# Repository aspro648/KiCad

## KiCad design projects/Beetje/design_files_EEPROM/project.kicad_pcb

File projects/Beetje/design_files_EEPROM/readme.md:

Beetje Blok Template

Based on https://jeelabs.org/2009/09/19/memory-plug-v1/

https://playground.arduino.cc/code/I2CEEPROM
https://www.instructables.com/id/Add-I2C-EEPROM-to-Arduino/
https://learn.sparkfun.com/tutorials/reading-and-writing-serial-eeproms

Bill Of Materials
----------------
  
- 1 ea., Perfect Purple PCB from OSH Park, with not so perfect layout from [project.kicad_pcb](project.kicad_pcb) file.
- 1 ea., C1 CAP CER 0.1UF 50V X7R 0805, https://www.digikey.com/short/j58qjp
- 1 ea., R1, R2 4K7 0805 SMD Resistor, https://www.digikey.com/short/j2d0wd

- 1 ea., U1, 24LC1025-I/SN-ND 1Mbit 8-SOIC, https://www.digikey.com/short/jwmp8v ($2.95), or
- 1 ea., U1, CAT24M01WI-GT3IC 1Mbit 8-SOIC, https://www.digikey.com/short/jwmpp7 ($1.33), or
RM24C512C FRAM 512K, https://www.digikey.com/short/jwmpqm ???
 or
- 1 ea., U1, IC EEPROM 1M I2C 400KHZ 8SOIC, https://www.digikey.com/short/jf10h0

Revisions
----------------
0.1 Sep 2018 Footprints from 0603 to 0805

License
----------------
[Attribution-ShareAlike 3.0 United States (CC BY-SA 3.0 US)](https://creativecommons.org/licenses/by-sa/3.0/us/)

You are free to:

- Share — copy and redistribute the material in any medium or format
- Adapt — remix, transform, and build upon the material

Under the following terms:

- Attribution — You must give appropriate credit, provide a link to the license, and indicate if changes were made. You may do so in any reasonable manner, but not in any way that suggests the licensor endorses you or your use.
- ShareAlike — If you remix, transform, or build upon the material, you must distribute your contributions under the same license as the original.

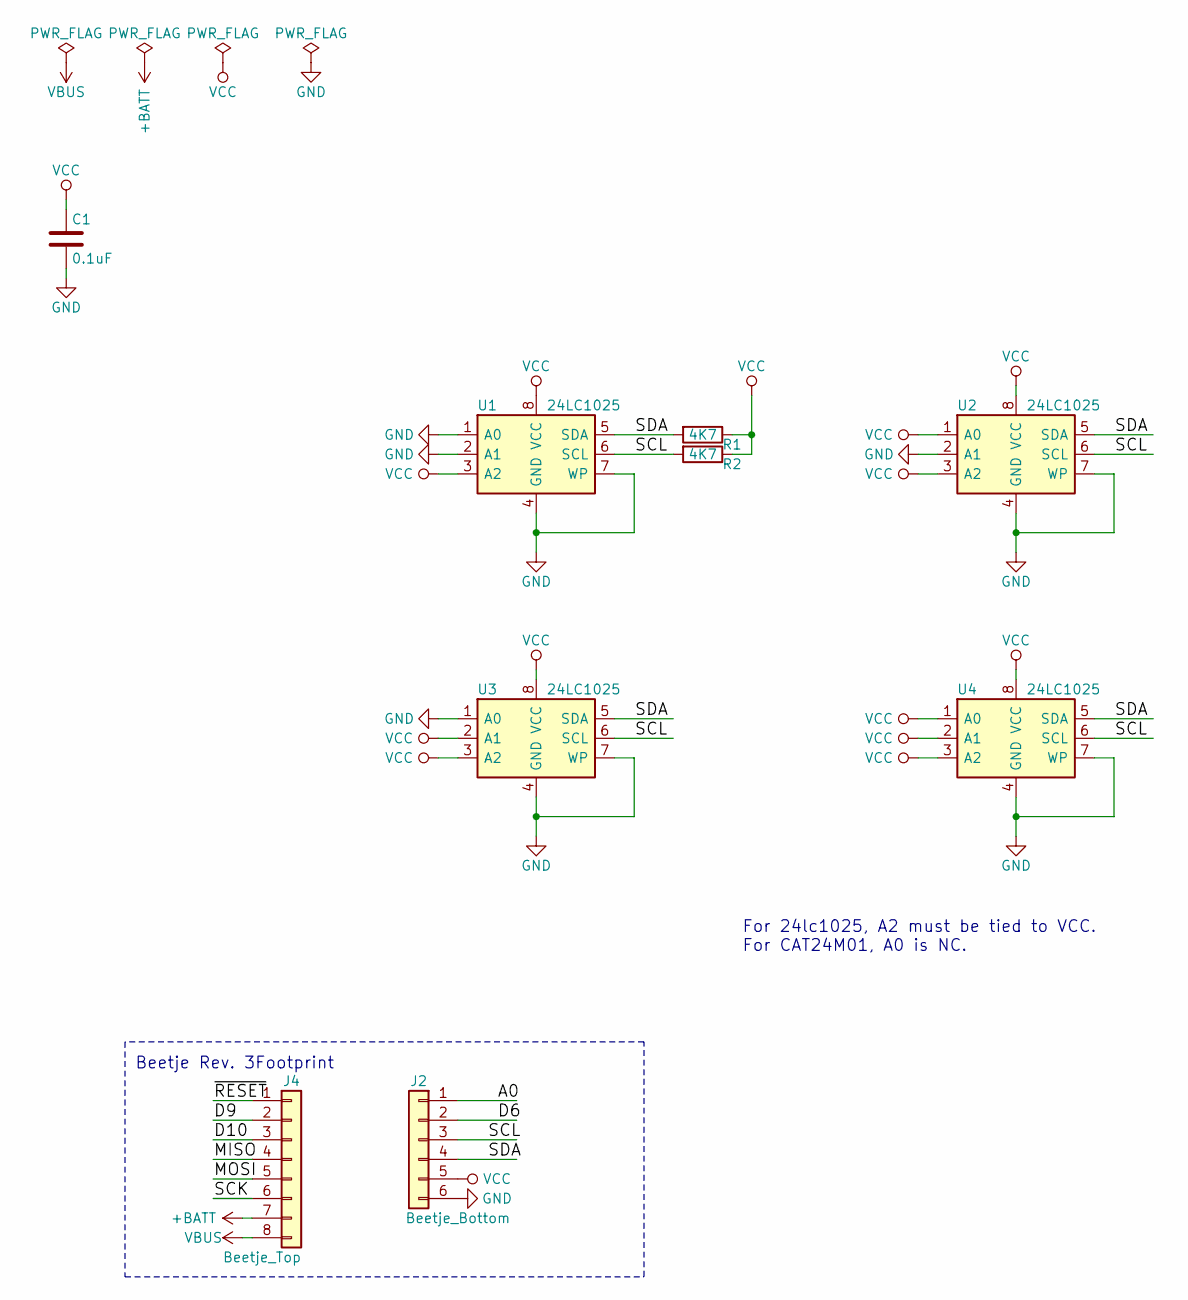
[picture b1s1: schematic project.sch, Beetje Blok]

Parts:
C1: 0.1uF; C_0603
J2: Beetje_Bottom; Pin_Header_Straight_1x06_Pitch2.54mm
J4: Beetje_Top; Pin_Header_Straight_1x08_Pitch2.54mm
R1, R2: 4K7; R_0603
U1, U2, U3, U4: 24LC1025; SOIC-8_3.9x4.9mm_Pitch1.27mm

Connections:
+BATT: J4.7
/A0: J2.1
/D6: J2.2
/D9: J4.2
/D10: J4.3
/MISO: J4.4
/MOSI: J4.5
/SCK: J4.6
/SCL: J2.3, R2.2, U1.6 (SCL), U2.6 (SCL), U3.6 (SCL), U4.6 (SCL)
/SDA: J2.4, R1.2, U1.5 (SDA), U2.5 (SDA), U3.5 (SDA), U4.5 (SDA)
/~RESET: J4.1
GND: C1.2, J2.6, U1.1 (A0), U1.2 (A1), U1.4 (GND), U1.7 (WP), U2.2 (A1), U2.4 (GND), U2.7 (WP), U3.1 (A0), U3.4 (GND), U3.7 (WP), U4.4 (GND), U4.7 (WP)
VBUS: J4.8
VCC: C1.1, J2.5, R1.1, R2.1, U1.3 (A2), U1.8 (VCC), U2.1 (A0), U2.3 (A2), U2.8 (VCC), U3.2 (A1), U3.3 (A2), U3.8 (VCC), U4.1 (A0), U4.2 (A1), U4.3 (A2), U4.8 (VCC)

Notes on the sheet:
Beetje Rev. 3Footprint
For 24lc1025, A2 must be tied to VCC. For CAT24M01, A0 is NC.

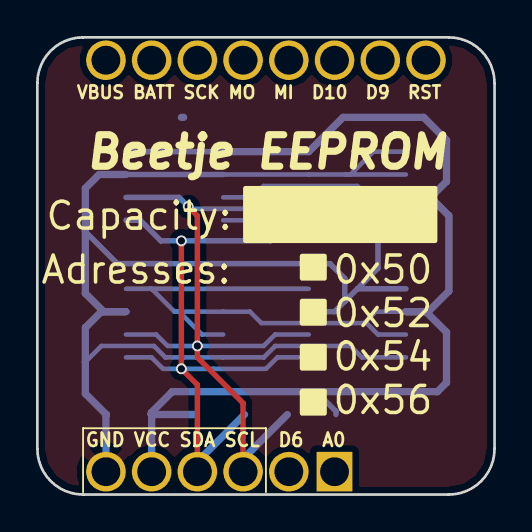
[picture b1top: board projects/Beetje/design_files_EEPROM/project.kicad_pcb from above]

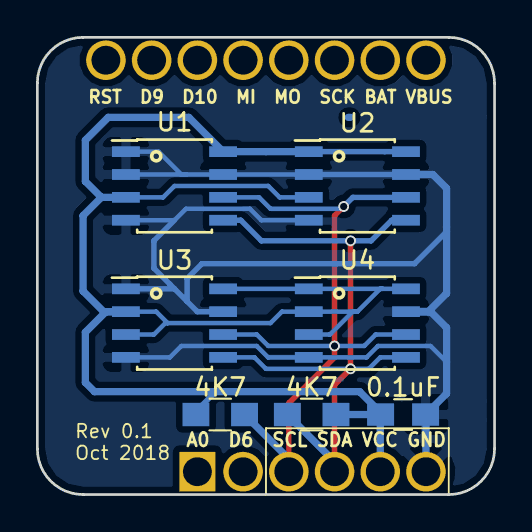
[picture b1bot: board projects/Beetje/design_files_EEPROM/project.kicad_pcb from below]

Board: 2 copper layers, 25.4 x 25.4 mm, 9 parts (7 on the bottom side), 4 nets.

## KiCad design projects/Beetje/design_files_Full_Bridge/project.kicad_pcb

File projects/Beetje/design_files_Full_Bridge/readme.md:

Beetje Full Bridge

Full bridge motor driver using Ti DRV8871.  Capable of 6.5V ~ 45V output at 3.6A.  Current can be limited by resistor settings.

D10	D11	MTR_A 	MTR_B
0	0	Hi-Z	Hi-Z
0	1	L 		H
1	0	H 		L
1	1	L 		L   (brake, low-side slow decay)

Project website: https://hackaday.io/project/160638-beetje-bloks

Bill Of Materials
----------------
  
- 1 ea., Perfect Purple PCB from OSH Park, with not so perfect layout from [project.kicad_pcb](project.kicad_pcb) file.
- 1 ea., U1 DRV8871 IC MOTOR DRIVER, https://www.digikey.com/short/p877rm 
- 1 ea., U2 MCP2031 I2C ADC SO23-5, MCP3021A1T-E/OT (address 0x49) https://www.digikey.com/short/p877wq
- 1 ea., CAP CER 0.1UF 50V X7R 0805, https://www.digikey.com/short/pq0ncp 
- 1 ea., CAP 47UF 63V SMD 8.3mm, https://www.digikey.com/short/p87c9p
- 1 ea., D6 LED SMD 0805, https://www.digikey.com/short/jwf4nw
- 1 ea., R1 SMD 0805, Current limiting 
	- 3.5A  18K Ohm, https://www.digikey.com/short/p8779m
	- 3A 22K Ohm, https://www.digikey.com/short/p8779n
	- 2A 33K Ohm, https://www.digikey.com/short/p87791
	- 1A 62K Ohm, https://www.digikey.com/short/p877bq
- 1 ea., R2 1K SMD 0805, https://www.digikey.com/short/j2d0wt
- 2 ea., J1, J3 TERM BLOCK PCB 2POS 5.0MM GREEN, Phoenix 1935161 https://www.digikey.com/short/jnrmvw
- 1 ea., 64-pin header(enough for 4.5 boards) Mill-max 311-43-164-41-001000, https://www.digikey.com/short/jnqdm2

Revisions
------------------
0.1 Rename to Full bridge, because that is what it is, I learned.

License
----------------
[Attribution-ShareAlike 3.0 United States (CC BY-SA 3.0 US)](https://creativecommons.org/licenses/by-sa/3.0/us/)

You are free to:

- Share — copy and redistribute the material in any medium or format
- Adapt — remix, transform, and build upon the material

Under the following terms:

- Attribution — You must give appropriate credit, provide a link to the license, and indicate if changes were made. You may do so in any reasonable manner, but not in any way that suggests the licensor endorses you or your use.
- ShareAlike — If you remix, transform, or build upon the material, you must distribute your contributions under the same license as the original.

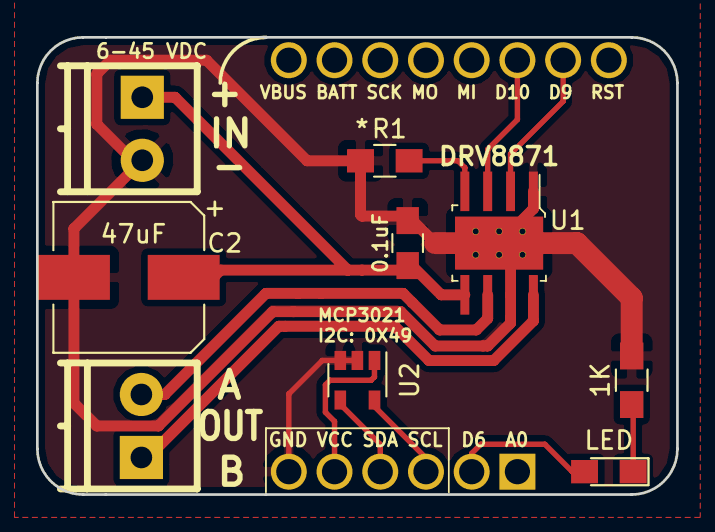
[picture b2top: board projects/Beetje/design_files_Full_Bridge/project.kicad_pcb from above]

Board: 2 copper layers, 35.6 x 25.4 mm, 12 parts (0 on the bottom side), 12 nets.

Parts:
C1: 0.1uF; C_0805_HandSoldering
C2: 47uF; CP_Elec_8x10
D6: LED; LED_0805_HandSoldering
J1: Conn_01x02; terminal_mirror
J2: Beetje_Bottom
J3: Conn_01x02; terminal
J4: Beetje_Top
R1: *; R_0805_HandSoldering
R2: 1K; R_0805_HandSoldering
U1: DRV8871DDA; PowerSOIC-8_W3.9mm
U2: MCP3021; SOT-23-5
VAL: MadeInOregonRev25

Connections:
/D6: D6.2, J2.2
/D9: J4.2, U1.2
/D10: J4.3, U1.3
/MTR_A: J3.2, U1.6
/MTR_B: J3.1, U1.8
/SCL: J2.3, U2.5
/SDA: J2.4, U2.4
/VMTR: C1.1, C2.1, J1.1, U1.5
GND: C1.2, C2.2, J1.2, J2.6, R1.2, R2.1, U1.1, U1.7, U1.9, U2.2, U2.3
unnamed: D6.1, R2.2
unnamed: R1.1, U1.4
VCC: J2.5, U2.1

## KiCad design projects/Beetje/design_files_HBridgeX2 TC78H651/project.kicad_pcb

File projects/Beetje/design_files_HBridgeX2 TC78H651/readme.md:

Beetje H-Bridge

Project website: https://hackaday.io/project/160638-beetje-bloks

Bill Of Materials
----------------
  
- 1 ea., Perfect Purple PCB from OSH Park, with not so perfect layout from [project.kicad_pcb](project.kicad_pcb) file.
- 1 ea., TC78H651FNG IC MOTOR DRIVER 16TSSOP, https://www.digikey.com/short/z8r9nr
- 1 ea., CAP CER 10UF 25V 1206, https://www.digikey.com/short/j29pwm
- 1 ea., CAP CER 1UF 16V X7R 0805, https://www.digikey.com/short/z8dz2m
- 1 ea., TRIMMER 10K OHM 0.1W J LEAD TOP, https://www.digikey.com/short/zq5dpc
- 1 ea., D2 LED SMD 0805, https://www.digikey.com/short/jwf4nw
- 4 ea., R3-R8 10K SMD 0805, https://www.digikey.com/short/j2d0w4 
- 1 ea., R2 1K SMD 0805, https://www.digikey.com/short/j2d0wt
- 3 ea., J1, J3, J5 TERM BLOCK PCB 2POS 5.0MM GREEN, Phoenix 1935161 https://www.digikey.com/short/jnrmvw
- 1 ea., 64-pin header(enough for 4.5 boards) Mill-max 311-43-164-41-001000, https://www.digikey.com/short/jnqdm2

Revisions
------------------
0.3 Switched from TB6612FNG to TC78H651FNG, added potentiometer, removed MCP chip.

License
----------------
[Attribution-ShareAlike 3.0 United States (CC BY-SA 3.0 US)](https://creativecommons.org/licenses/by-sa/3.0/us/)

You are free to:

- Share — copy and redistribute the material in any medium or format
- Adapt — remix, transform, and build upon the material

Under the following terms:

- Attribution — You must give appropriate credit, provide a link to the license, and indicate if changes were made. You may do so in any reasonable manner, but not in any way that suggests the licensor endorses you or your use.
- ShareAlike — If you remix, transform, or build upon the material, you must distribute your contributions under the same license as the original.

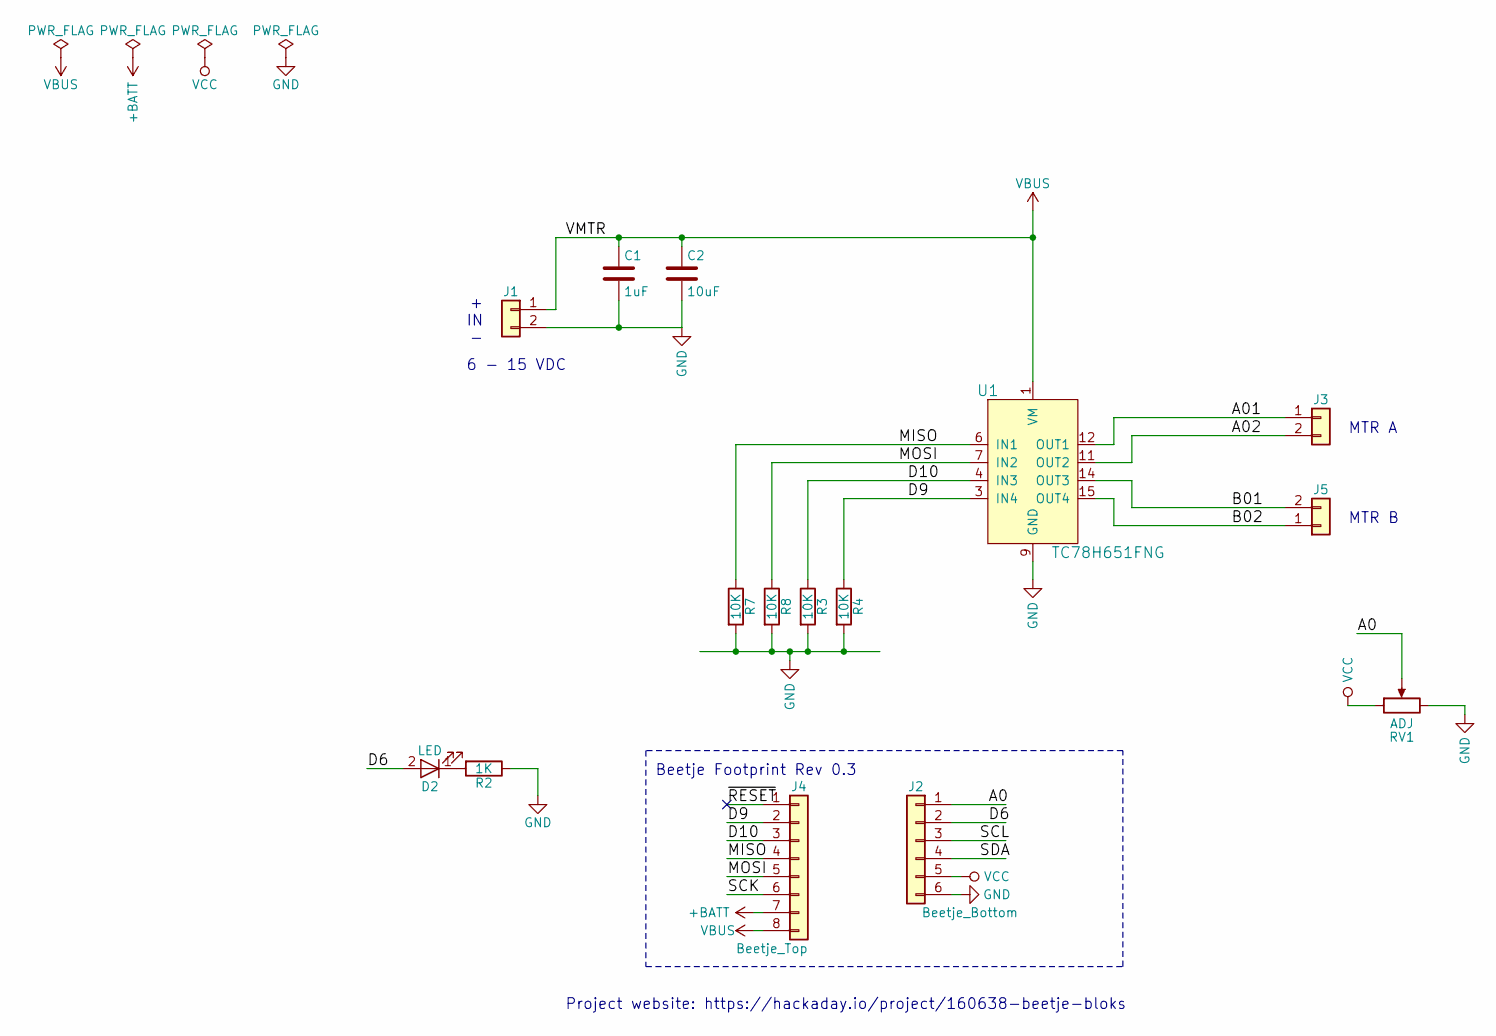
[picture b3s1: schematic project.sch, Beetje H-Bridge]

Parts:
C1: 1uF; C_0805_HandSoldering
C2: 10uF; C_1206
D2: LED; LED_0805_HandSoldering
J1: Conn_01x02; terminal_mirror
J2: Beetje_Bottom
J3, J5: Conn_01x02; terminal
J4: Beetje_Top
R2: 1K; R_0805_HandSoldering
R3, R4, R7, R8: 10K; R_0805_HandSoldering
RV1: ADJ
U1: TC78H651FNG; TSSOP-16_4.4x5mm_Pitch0.65mm

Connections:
+BATT: J4.7
/A0: J2.1, RV1.2
/A01: J3.1, U1.12 (OUT1)
/A02: J3.2, U1.11 (OUT2)
/B01: J5.2, U1.14 (OUT3)
/B02: J5.1, U1.15 (OUT4)
/D6: D2.2 (A), J2.2
/D9: J4.2, R4.1, U1.3 (IN4)
/D10: J4.3, R3.1, U1.4 (IN3)
/MISO: J4.4, R7.1, U1.6 (IN1)
/MOSI: J4.5, R8.1, U1.7 (IN2)
/SCK: J4.6
/SCL: J2.3
/SDA: J2.4
/~RESET: J4.1
GND: C1.2, C2.2, J1.2, J2.6, R2.1, R3.2, R4.2, R7.2, R8.2, RV1.3, U1.9 (GND)
unnamed: D2.1 (K), R2.2
VBUS: C1.1, C2.1, J1.1, J4.8, U1.1 (VM)
VCC: J2.5, RV1.1

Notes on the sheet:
Beetje Footprint Rev 0.3
Project website: https://hackaday.io/project/160638-beetje-bloks
+ IN -
MTR A
MTR B
6 - 15 VDC

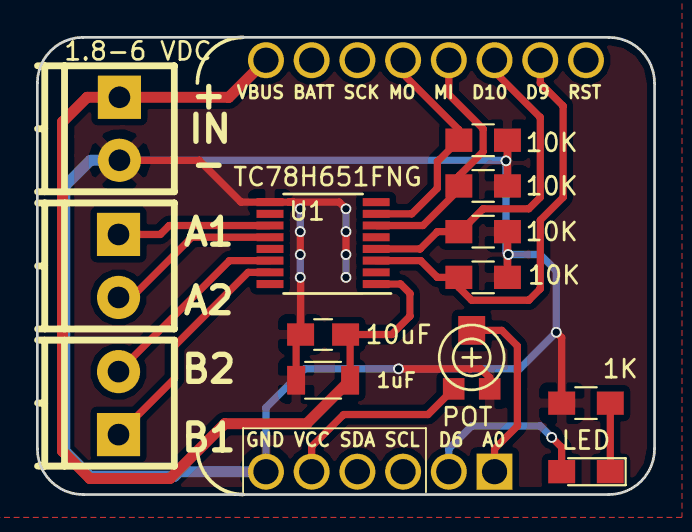
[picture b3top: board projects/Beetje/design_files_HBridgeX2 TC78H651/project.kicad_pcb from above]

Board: 2 copper layers, 34.3 x 25.4 mm, 16 parts (0 on the bottom side), 14 nets.

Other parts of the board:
VAL: MadeInOregonRev25

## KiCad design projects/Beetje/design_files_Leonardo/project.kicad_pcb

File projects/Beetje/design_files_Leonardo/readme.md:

Leo, the Arduino Leonardo clone done in KiCad.

https://rheingoldheavy.com/arduino-from-scratch-part-5-selecting-comparator-parts/

Bill Of Materials
----------------
  
- 1 ea., Perfect Purple PCB from OSH Park, with not so perfect layout from kicad.pcb file.
- 1 ea., U1 IC REG LINEAR 3.3V 150MA SOT23-5, LP2985-33DBVRG4, https://www.digikey.com/short/j29pqr
- 1 ea., U2 IC OPAMP GP 1MHZ RRO 8VSSOP, LMV358IDGKR, https://www.digikey.com/short/j29pj7
- 1 ea., U3 IC REG LINEAR 5V 1A SOT223 NCP1117ST50T3G, https://www.digikey.com/short/j29pqc
- 1 ea., U4 ATMEGA32U4-AU, IC MCU 8BIT 32KB FLASH 44TQFP, https://www.digikey.com/short/jb25pc
- 1 ea., Q1 MOSFET P-CH 20V 2A SSOT3, FDN340P, https://www.digikey.com/short/j29ppj

- 1 ea., Y1 CER RES 16.0000MHZ 15PF SMD, CSTCE16M0V53-R0, https://www.digikey.com/short/j2b9cm
- 2 ea., C1, C5 CAP CER 1UF SMD 0805
- 1 ea., C2 CAP CER 22pF SMD 0805
- 2 ea., C3, C6, C7 CAP CER 10UF 25V 1206, https://www.digikey.com/short/j29pwm
- 1 ea., C4 CAP CER 0.1UF SMD 0805

- 4 ea., D1-D4 SMD LED 0805, https://www.digikey.com/short/jwj4rb
- 1 ea., F1 PTC 1206, Bel 0ZCJ0025AF2E, https://www.digikey.com/short/jfcbc8
- 2 ea., RV1, RV2 VARISTOR 	VARISTOR 10.8V 40A 0805, https://www.digikey.com/short/jwj45d
- 4 ea., R1-R4 Resistor 1K OHM SMD 0805, https://www.digikey.com/short/j2d0wt
- 2 ea., R5, R8 Resistor 10K OHM SMD 0805, https://www.digikey.com/short/j2d0w4
- 2 ea., R6, R7 Resistor 22 OHM SMD 0805, https://www.digikey.com/short/jwj45j
- 1 ea., R9 Resistor 1M OHM SMD 0603, 

- 1 ea., SW1 (yellow) SWITCH TACTILE SPST-NO 0.05A 12V, SW416-ND, https://www.digikey.com/short/jwj4m9
- or (purple) KSEM31J LFS https://www.digikey.com/short/jnqh3m
- 1 ea., X3, CONN RCPT MICRO USB R/A SMD, Molex 1050170001, https://www.digikey.com/short/jb2205
- 1 ea., J1 Barrel Jack, https://www.digikey.com/short/j2fz43
- 1 ea., 6-Pin header, https://www.digikey.com/short/jwj4w4
- 2 ea., 8-Pin header, https://www.digikey.com/short/jwj4dp
- 1 ea., 10-Pin header, https://www.digikey.com/short/jwj4n7
- 4 ea., Rubber feet, https://www.digikey.com/short/jntvm1 or https://www.digikey.com/short/jntvbz

License
----------------
[Attribution-ShareAlike 3.0 United States (CC BY-SA 3.0 US)](https://creativecommons.org/licenses/by-sa/3.0/us/)

You are free to:

- Share — copy and redistribute the material in any medium or format
- Adapt — remix, transform, and build upon the material

Under the following terms:

- Attribution — You must give appropriate credit, provide a link to the license, and indicate if changes were made. You may do so in any reasonable manner, but not in any way that suggests the licensor endorses you or your use.
- ShareAlike — If you remix, transform, or build upon the material, you must distribute your contributions under the same license as the original.

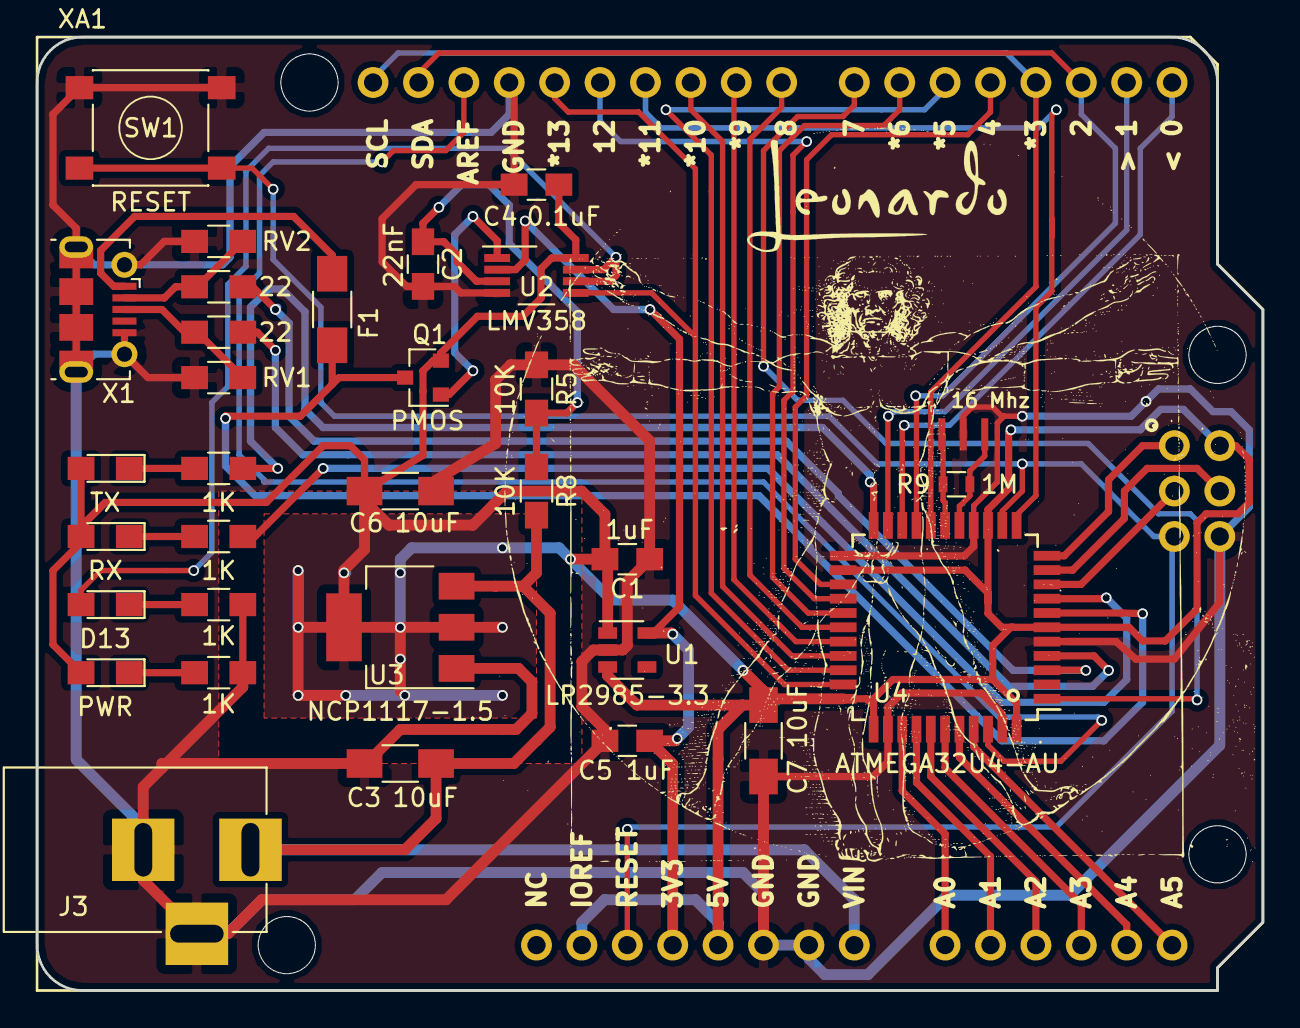
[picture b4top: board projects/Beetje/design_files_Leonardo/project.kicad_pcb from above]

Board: 2 copper layers, 68.6 x 53.3 mm, 34 parts (0 on the bottom side), 46 nets.

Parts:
C1, C5: 1uF; C_0805_HandSoldering
C2: 22nF; C_0805_HandSoldering
C3, C6, C7: 10uF; C_1206_HandSoldering
C4: 0.1uF; C_0805_HandSoldering
D1: PWR; LED_0805_HandSoldering
D2: TX; LED_0805_HandSoldering
D3: RX; LED_0805_HandSoldering
D4: D13; LED_0805_HandSoldering
F1: Polyfuse; R_1206_HandSoldering
J3: Barrel_Jack; BARREL_JACK
Q1: PMOS; SOT-23
R1, R2, R3, R4: 1K; R_0805_HandSoldering
R5, R8: 10K; R_0805_HandSoldering
R6, R7: 22; R_0805_HandSoldering
R9: 1M; R_0603
RV1, RV2: Varistor; R_0805_HandSoldering
SW1: RESET; SW_SPST_PTS645
U1: LP2985-3.3; SOT-23-5
U2: LMV358; VSSOP-8_3.0x3.0mm_Pitch0.65mm
U3: NCP1117-1.5; SOT-223-3_TabPin2
U4: ATMEGA32U4-AU; TQFP-44_10x10mm_Pitch0.8mm
VAL: MadeInOregonRev25
X1: USB_OTG; USB_Micro-B_Molex-105017-0001
XA1: Arduino_Leonardo_Shield
Y1: 16 Mhz; Resonator_SMD_CTSC_1.3mmx3.2mm

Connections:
+3V3: C5.1, U1.5, U2.2, XA1.3V3
+5V: C1.1, C4.1, C6.1, C7.1, D1.2, D2.2, D3.2, Q1.2, U1.1, U1.3, U2.8, U3.2, U4.6, U4.14, U4.24, U4.33, U4.34, U4.44, XA1.5V1, XA1.5V2, XA1.IORF
/A0: U4.36, XA1.A0
/A1: U4.37, XA1.A1
/A2: U4.38, XA1.A2
/A3: U4.39, XA1.A3
/A4: U4.40, XA1.A4
/A5: U4.41, XA1.A5
/AREF: U4.42, XA1.AREF
/D0: U4.20, XA1.D0
/D1: U4.21, XA1.D1
/D4: U4.25, XA1.D4
/D5: U4.31, XA1.D5
/D6: U4.27, XA1.D6
/D7: U4.1, XA1.D7
/D8: U4.28, XA1.D8
/D9: U4.29, XA1.D9
/D10: U4.30, XA1.D10
/D11: U4.12, XA1.D11
/D12: U4.26, XA1.D12
/D13: U2.5, U4.32, XA1.D13
/D+: R6.1, U4.4
/D-: R7.1, U4.3
/MISO: U4.11, XA1.MISO
/MOSI: U4.10, XA1.MOSI
/RXLED: R3.1, U4.8
/SCK: U4.9, XA1.SCK
/SCL: U4.18, XA1.D3, XA1.SCL
/SDA: U4.19, XA1.D2, XA1.SDA
/TXLED: R2.1, U4.22
/VIN: C3.1, J3.1, R8.2, U3.3, XA1.VIN
/~RESET: SW1.2, U4.13, XA1.RST1, XA1.RST2
GND: C1.2, C2.2, C3.2, C4.2, C5.2, C6.2, C7.2, J3.2, J3.3, R1.2, R4.2, R5.1, RV1.2, RV2.2, SW1.1, U1.2, U2.4, U3.1, U4.5, U4.15, U4.23, U4.35, U4.43, X1.5, X1.6, XA1.GND1, XA1.GND2, XA1.GND3, XA1.GND4, Y1.2
unnamed: C2.1, R5.2, R8.1, U2.3
unnamed: D1.1, R1.1
unnamed: D2.1, R2.2
unnamed: D3.1, R3.2
unnamed: D4.1, R4.1
unnamed: D4.2, U2.6, U2.7
unnamed: F1.2, X1.1
unnamed: Q1.1, U2.1
unnamed: R6.2, RV1.1, X1.3
unnamed: R7.2, RV2.1, X1.2
unnamed: R9.1, U4.16, Y1.3
unnamed: R9.2, U4.17, Y1.1
VBUS: F1.1, Q1.3, U4.7

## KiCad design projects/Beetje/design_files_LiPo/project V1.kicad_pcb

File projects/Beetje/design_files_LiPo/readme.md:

Beetje LiPo Battery Blok

Project website: https://hackaday.io/project/160638-beetje-bloks

Based on Adafruit's [Adafruit Pro Trinket LiPoly/LiIon Backpack](https://learn.adafruit.com/adafruit-pro-trinket-lipoly-slash-liion-backpack/downloads)

Try adding TVS: https://www.digikey.com/product-detail/en/stmicroelectronics/SM2T3V3A/497-7878-1-ND/1883813
https://www.digikey.com/product-detail/en/comchip-technology/CPDQC3V3T-HF/641-1893-1-ND/7100791
Update to 0805 parts

Bill Of Materials
----------------
  
- 1 ea., Perfect Purple PCB from OSH Park, with not so perfect layout from [project.kicad_pcb](project.kicad_pcb) file.
- 2 ea., CAP CER 10UF 25V 1206, https://www.digikey.com/short/j29pwm
- 1 ea., U1 IC LI-ION/LI-POLY CTRLR 10MSOP, MCP73833T-AMI/UN, https://www.digikey.com/short/zjdzwb
- 1 ea., BATTERY LITHIUM 3.7V 150MA, TinyCircuits ASR00003, https://www.digikey.com/short/jf925w
- 1 ea., JST SH CONN HEADER SH 2POS 1MM, SM02B-SRSS-TB(LF)(SN), https://www.digikey.com/short/jfdccc
- 1 ea., JST PH CONN HEADER PH SIDE 2POS 2MM, S2B-PH-K-S(LF)(SN), https://www.digikey.com/short/jfdct5
- 1 ea., R4 Resistor 10K SMD 0805, https://www.digikey.com/short/j2d0w4
- 1 ea., R5 Resistor 4K7 SMD 0805, https://www.digikey.com/short/zjdz12
- 3 ea., R1-R3 Resistor 1K SMD 0805, https://www.digikey.com/short/j2d0wt
- 1 ea., D1 LED red SMD 0805, https://www.digikey.com/short/j20zct
- 1 ea., D2 LED green SMD 0805, https://www.digikey.com/short/j20p1h
- 1 ea., D3 LED ORANGE CLEAR 0805 SMD, https://www.digikey.com/short/qjwthb
- 2 ea., D4 DIODE SCHOTTKY 20V 1A SOD123FL, MBR120ESFT1G, https://www.digikey.com/short/jnqvz9
- 1 ea., SMD SPST switch, C&K JS102011SAQN, Digikey 401-1999-1-ND

Revisions
------------------
- 0.0 Aug 2018 Initial build
- 0.1 Sep 2018 Switch to 0805 packages. Swap J1 & J3 connector polarities.  Add power switch and reverse current diode.
- 0.2 Sep 2018 Pinout to match 32U4 rev 0.3, added pour planes per datasheet, rerouted.
- 0.3 Sep 2018 Fixed LED footprints.
- 0.5 Apr 2020 Switch to MCP7833 Chip, enlarged header holes.
- 0.6 Apr 2020 Switched silkscreen on CHG/DONE LEDs

License
----------------
[Attribution-ShareAlike 3.0 United States (CC BY-SA 3.0 US)](https://creativecommons.org/licenses/by-sa/3.0/us/)

You are free to:

- Share — copy and redistribute the material in any medium or format
- Adapt — remix, transform, and build upon the material

Under the following terms:

- Attribution — You must give appropriate credit, provide a link to the license, and indicate if changes were made. You may do so in any reasonable manner, but not in any way that suggests the licensor endorses you or your use.
- ShareAlike — If you remix, transform, or build upon the material, you must distribute your contributions under the same license as the original.

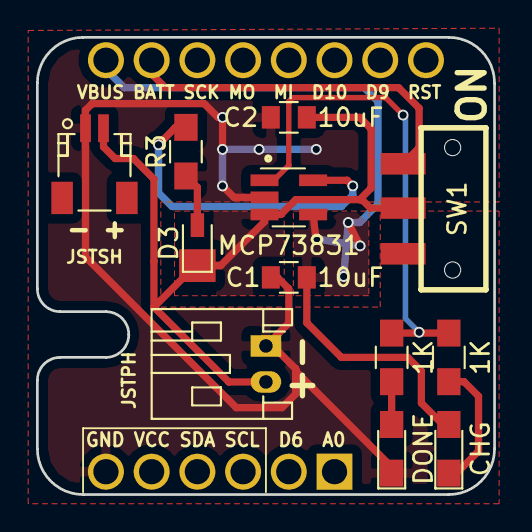
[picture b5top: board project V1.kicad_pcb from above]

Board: 2 copper layers, 25.4 x 25.4 mm, 15 parts (0 on the bottom side), 8 nets.

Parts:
C1, C2: 10uF; C_0805
D1: CHG; LED_0805_HandSoldering
D2: DONE; LED_0805_HandSoldering
D3: D_TVS; D_0805
J1: JSTSH; JST_SH_SM02B-SRSS-TB_02x1.00mm_Angled
J2: Beetje_Bottom
J3: JSTPH; JST_PH_S2B-PH-K_02x2.00mm_Angled
J4: Beetje_Top
R1, R2: 1K; R_0805_HandSoldering
R3: 10K; R_0805_HandSoldering
SW1: SW_SPDT; SPST_SMD
U1: MCP73831; SOT-23-5_HandSoldering
VAL: MadeInOregonRev25

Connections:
+BATT: J4.7, SW1.3
GND: C1.2, C2.2, D2.1, D3.2, J1.1, J2.6, J3.1, R3.2, U1.2
unnamed: C2.1, D3.1, J1.2, J3.2, SW1.2, U1.3
unnamed: D1.1, R1.1
unnamed: D2.2, R2.1
unnamed: R1.2, R2.2, U1.1
unnamed: R3.1, U1.5
VBUS: C1.1, D1.2, J4.8, U1.4

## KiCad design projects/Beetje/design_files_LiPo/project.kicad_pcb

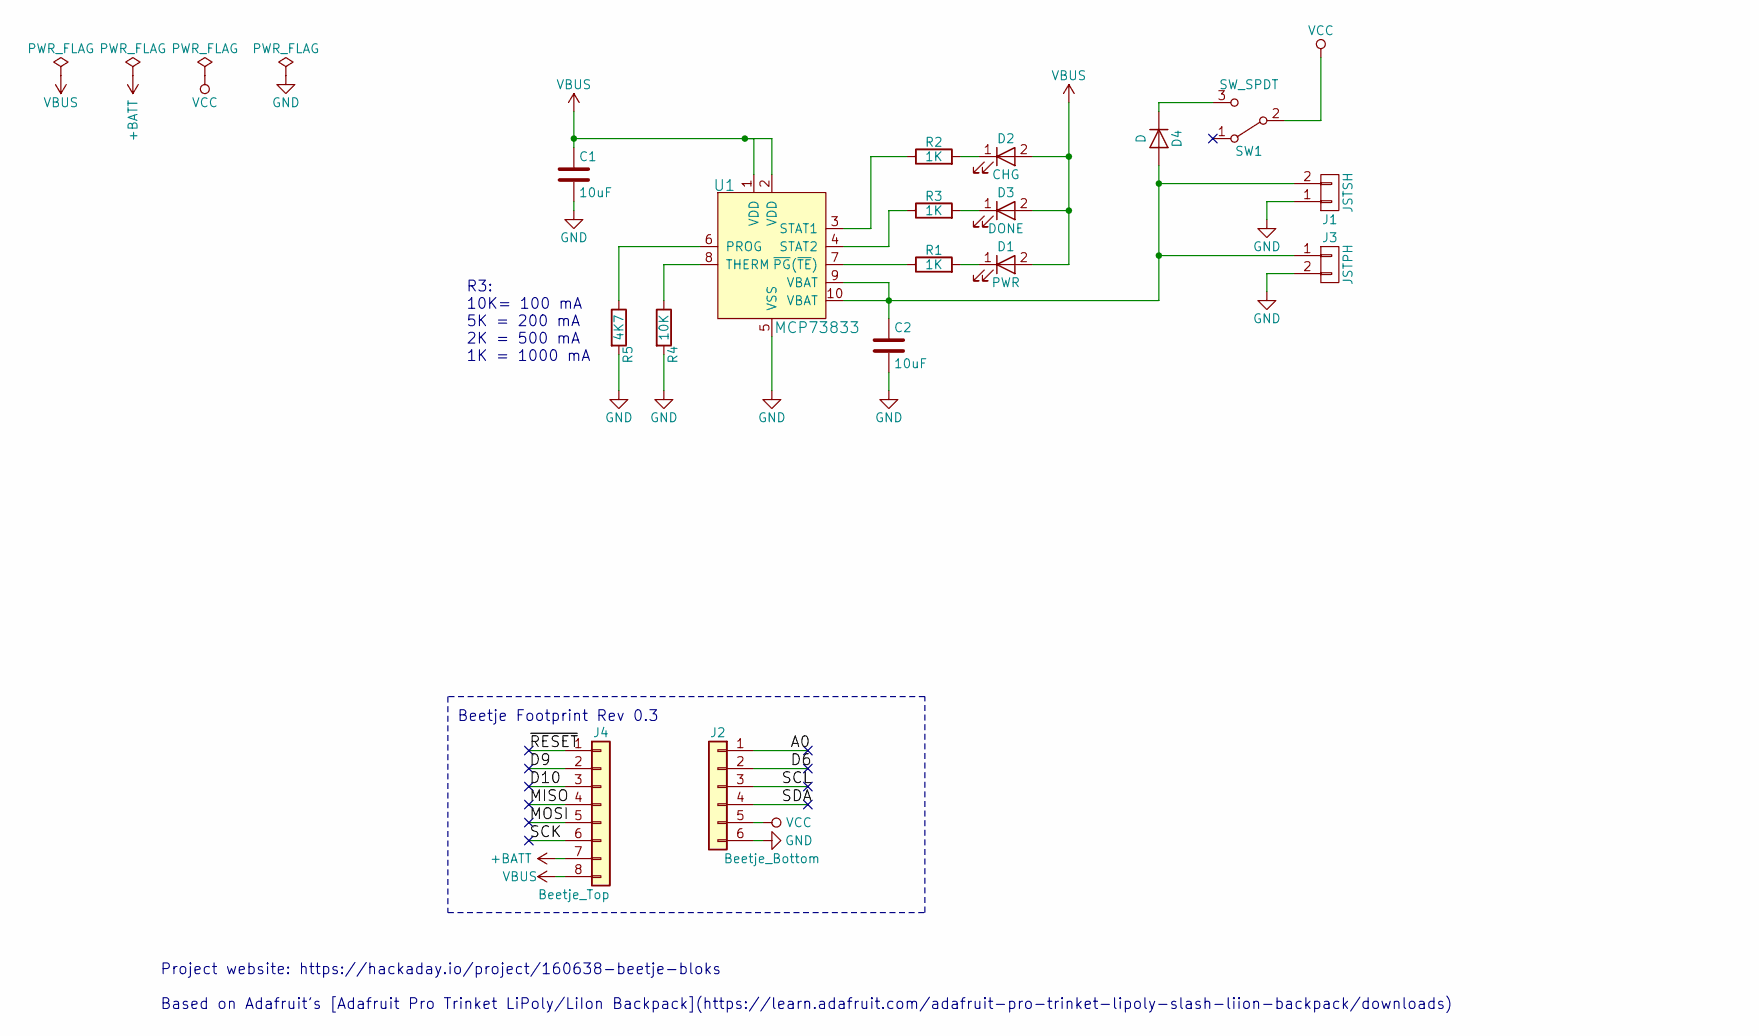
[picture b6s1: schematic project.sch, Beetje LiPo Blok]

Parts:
C1, C2: 10uF; C_0805
D1: PWR; LED_0805_HandSoldering
D2: CHG; LED_0805_HandSoldering
D3: DONE; LED_0805_HandSoldering
D4: D; D_SOD-123F
J1: JSTSH; JST_SH_SM02B-SRSS-TB_02x1.00mm_Angled
J2: Beetje_Bottom
J3: JSTPH; JST_PH_S2B-PH-K_02x2.00mm_Angled
J4: Beetje_Top
R1, R2, R3: 1K; R_0805_HandSoldering
R4: 10K; R_0805_HandSoldering
R5: 4K7; R_0805_HandSoldering
SW1: SW_SPDT; SPST_SMD
U1: MCP73833; MSOP-10_3x3mm_Pitch0.5mm

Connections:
+BATT: J4.7
/A0: J2.1
/D6: J2.2
/D9: J4.2
/D10: J4.3
/MISO: J4.4
/MOSI: J4.5
/SCK: J4.6
/SCL: J2.3
/SDA: J2.4
/~RESET: J4.1
GND: C1.2, C2.2, J1.1, J2.6, J3.2, R4.2, R5.2, U1.5 (VSS)
unnamed: C2.1, D4.2 (A), J1.2, J3.1, U1.9 (VBAT), U1.10 (VBAT)
unnamed: D1.1 (K), R1.2
unnamed: D2.1 (K), R2.2
unnamed: D3.1 (K), R3.2
unnamed: D4.1 (K), SW1.3 (C)
unnamed: R1.1, U1.7 (~PG~(~TE~))
unnamed: R2.1, U1.3 (STAT1)
unnamed: R3.1, U1.4 (STAT2)
unnamed: R4.1, U1.8 (THERM)
unnamed: R5.1, U1.6 (PROG)
VBUS: C1.1, D1.2 (A), D2.2 (A), D3.2 (A), J4.8, U1.1 (VDD), U1.2 (VDD)
VCC: J2.5, SW1.2 (B)

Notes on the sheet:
Beetje Footprint Rev 0.3
R3: 10K= 100 mA 5K = 200 mA 2K = 500 mA 1K = 1000 mA
Project website: https://hackaday.io/project/160638-beetje-bloks Based on Adafruit's [Adafruit Pro Trinket LiPoly/LiIon Backpack](https://learn.adafruit.com/adafruit-pro-trinket-lipoly-slash-liion-backpack/downloads)

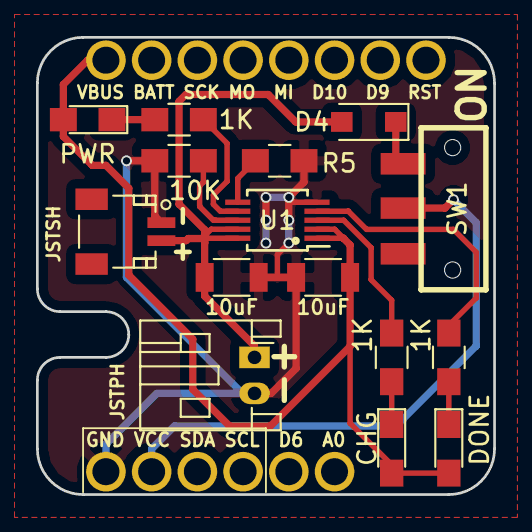
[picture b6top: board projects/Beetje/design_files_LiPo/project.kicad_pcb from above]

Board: 2 copper layers, 25.4 x 25.4 mm, 18 parts (0 on the bottom side), 13 nets.

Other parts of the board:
VAL: MadeInOregonRev25

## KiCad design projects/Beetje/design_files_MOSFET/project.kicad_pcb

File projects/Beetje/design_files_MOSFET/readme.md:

Beetje MOSFET

Project website: https://hackaday.io/project/160638-beetje-bloks

Bill Of Materials
----------------
  
- 1 ea., Perfect Purple PCB from OSH Park, with not so perfect layout from [project.kicad_pcb](project.kicad_pcb) file.
- 1 ea., Q1 MOSFET IRLB8721, https://www.digikey.com/short/jwf4nn
- 1 ea., D1 DIODE SCHOTTKY 20V 1A SOD123FL, MBR120ESFT1G, https://www.digikey.com/short/j2r1f3
- 1 ea., D2 LED SMD 0805, https://www.digikey.com/short/jwf4nw
- 1 ea., R1 10K SMD 0805, https://www.digikey.com/short/j2d0w4 
- 1 ea., R2 1K SMD 0805, https://www.digikey.com/short/j2d0wt
- 2 ea., J1, J3 TERM BLOCK PCB 2POS 5.0MM GREEN, Phoenix 1935161 https://www.digikey.com/short/jnrmvw
-- (was - 2 ea., TERMINAL BLOCK 3.5MM 2POS PCB, https://www.digikey.com/short/7zj1f4)
- 1 ea., 64-pin header(enough for 4.5 boards) Mill-max 311-43-164-41-001000, https://www.digikey.com/short/jnqdm2

Revisions
------------------
0.1 Moved terminal blocks to avoid short on USB. Changed to 5mm terminal for 12 AWG wire.

License
----------------
[Attribution-ShareAlike 3.0 United States (CC BY-SA 3.0 US)](https://creativecommons.org/licenses/by-sa/3.0/us/)

You are free to:

- Share — copy and redistribute the material in any medium or format
- Adapt — remix, transform, and build upon the material

Under the following terms:

- Attribution — You must give appropriate credit, provide a link to the license, and indicate if changes were made. You may do so in any reasonable manner, but not in any way that suggests the licensor endorses you or your use.
- ShareAlike — If you remix, transform, or build upon the material, you must distribute your contributions under the same license as the original.

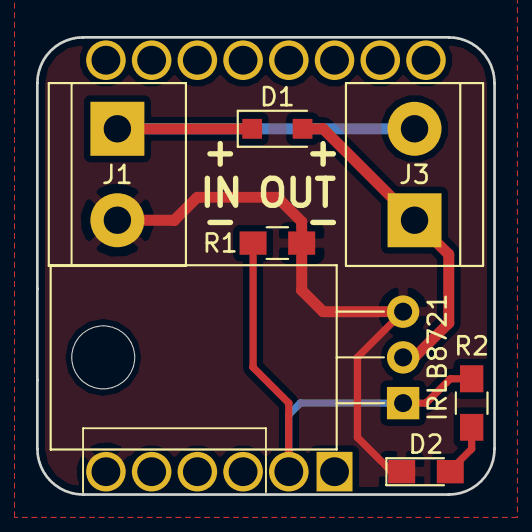
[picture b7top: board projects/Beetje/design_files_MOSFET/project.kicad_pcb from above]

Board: 2 copper layers, 25.4 x 25.4 mm, 10 parts (0 on the bottom side), 5 nets.

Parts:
D1: D; D_SOD-123F
D2: LED; LED_0805_HandSoldering
J1, J3: Conn_01x02; TerminalBlock_bornier-2_P5.08mm
J2: Beetje_Bottom
J4: Beetje_Top
Q1: IRLB8721; TO-220-3_Horizontal
R1: 10K; R_0805_HandSoldering
R2: 1K; R_0805_HandSoldering
VAL: MadeInOregonRev25

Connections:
/D6: J2.2, Q1.1, R1.1, R2.2
GND: D2.1, J1.2, J2.6, Q1.3, R1.2
unnamed: D1.1, J1.1, J3.2
unnamed: D1.2, J3.1, Q1.2
unnamed: D2.2, R2.1
